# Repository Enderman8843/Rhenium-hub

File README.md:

# Rhenium HUB
It is Hi-Speed USB HUB with USB2514B_B Chip and 24mhz crystal , With Support of USB C aswell as USB A

## How To Use ?
JUST PlUG IT INTO YOUR COMPUTER VIA THE INPUT

## PCB Layout and Render

| PCB | Schematics / Wiring |
|---|---|
| 
 |
|

| 3D View Rear | |
|---|---|

| Case |

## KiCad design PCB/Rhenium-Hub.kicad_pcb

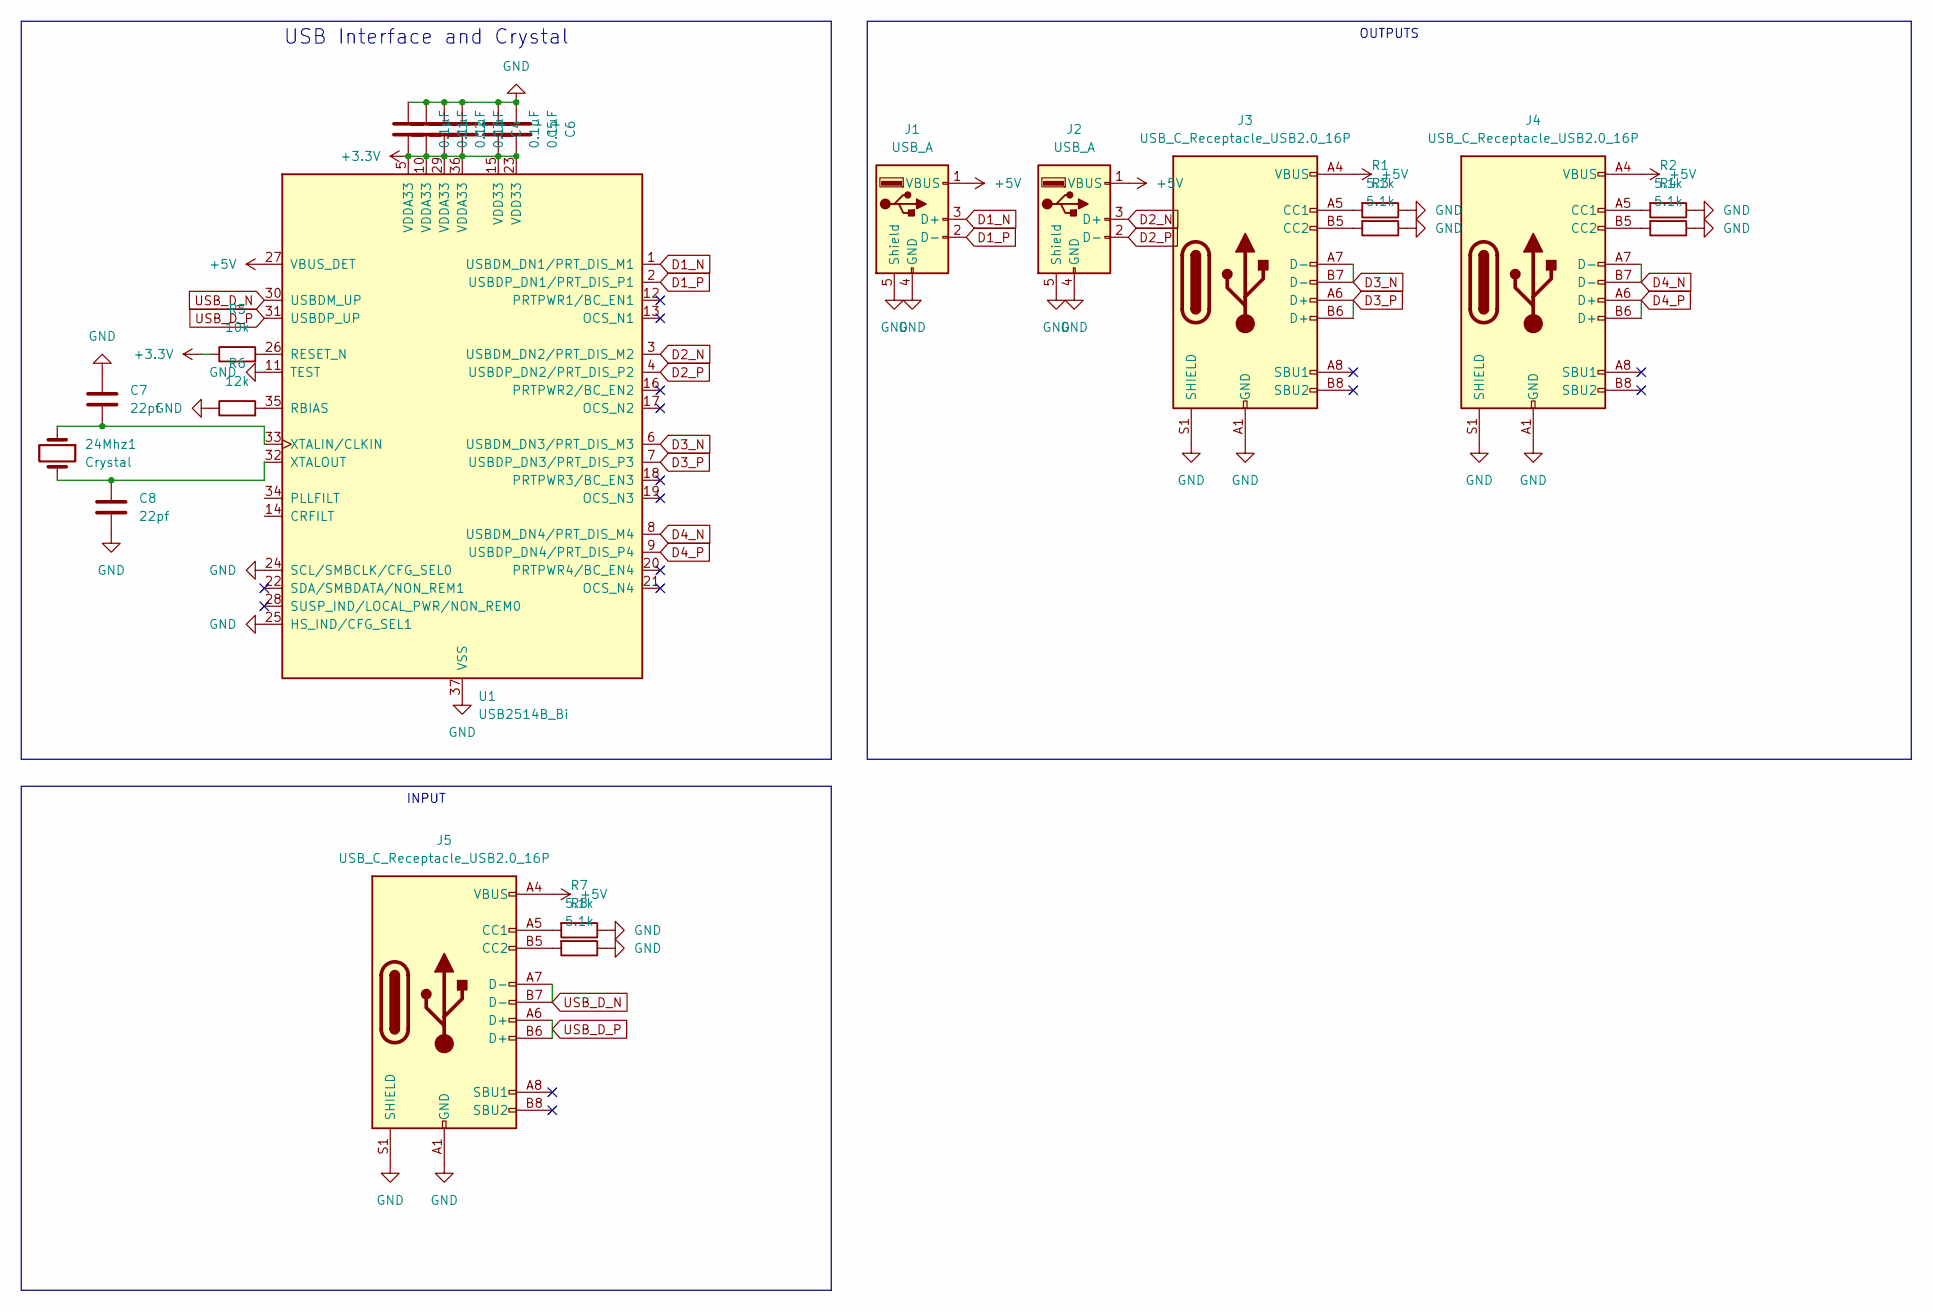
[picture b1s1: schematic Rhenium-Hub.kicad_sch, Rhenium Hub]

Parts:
24Mhz1: Crystal; Crystal_SMD_3225-4Pin_3.2x2.5mm
C1, C2, C3, C4, C5, C6: 0.1µF; C_0603_1608Metric
C7, C8: 22pf; C_0603_1608Metric
J1, J2: USB_A; USB_A_CNCTech_1001-011-01101_Horizontal
J3, J4, J5: USB_C_Receptacle_USB2.0_16P; USB_C_Receptacle_G-Switch_GT-USB-7010ASV
R1, R2, R3, R4, R7, R8: 5.1k; C_0603_1608Metric
R5: 10k; C_0603_1608Metric
R6: 12k; C_0603_1608Metric
U1: USB2514B_Bi; QFN-36-1EP_6x6mm_P0.5mm_EP3.7x3.7mm

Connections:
+3.3V: C1.2, C2.2, C3.2, C4.2, C5.2, C6.2, R5.1, U1.5 (VDDA33), U1.10 (VDDA33), U1.15 (VDD33), U1.23 (VDD33), U1.29 (VDDA33), U1.36 (VDDA33)
+5V: J1.1 (VBUS), J2.1 (VBUS), J3.A4 (VBUS), J3.A9 (VBUS), J3.B4 (VBUS), J3.B9 (VBUS), J4.A4 (VBUS), J4.A9 (VBUS), J4.B4 (VBUS), J4.B9 (VBUS), J5.A4 (VBUS), J5.A9 (VBUS), J5.B4 (VBUS), J5.B9 (VBUS), U1.27 (VBUS_DET)
D1_N: J1.3 (D+), U1.1 (USBDM_DN1/PRT_DIS_M1)
D1_P: J1.2 (D-), U1.2 (USBDP_DN1/PRT_DIS_P1)
D2_N: J2.3 (D+), U1.3 (USBDM_DN2/PRT_DIS_M2)
D2_P: J2.2 (D-), U1.4 (USBDP_DN2/PRT_DIS_P2)
D3_N: J3.A7 (D-), J3.B7 (D-), U1.6 (USBDM_DN3/PRT_DIS_M3)
D3_P: J3.A6 (D+), J3.B6 (D+), U1.7 (USBDP_DN3/PRT_DIS_P3)
D4_N: J4.A7 (D-), J4.B7 (D-), U1.8 (USBDM_DN4/PRT_DIS_M4)
D4_P: J4.A6 (D+), J4.B6 (D+), U1.9 (USBDP_DN4/PRT_DIS_P4)
GND: C1.1, C2.1, C3.1, C4.1, C5.1, C6.1, C7.1, C8.2, J1.4 (GND), J1.5 (Shield), J2.4 (GND), J2.5 (Shield), J3.A1 (GND), J3.A12 (GND), J3.B1 (GND), J3.B12 (GND), J3.S1 (SHIELD), J4.A1 (GND), J4.A12 (GND), J4.B1 (GND), J4.B12 (GND), J4.S1 (SHIELD), J5.A1 (GND), J5.A12 (GND), J5.B1 (GND), J5.B12 (GND), J5.S1 (SHIELD), R1.1, R2.1, R3.1, R4.1, R6.1, R7.1, R8.1, U1.11 (TEST), U1.24 (SCL/SMBCLK/CFG_SEL0), U1.25 (HS_IND/CFG_SEL1), U1.37 (VSS)
unnamed: J3.A5 (CC1), R1.2
unnamed: J3.B5 (CC2), R3.2
unnamed: J4.A5 (CC1), R2.2
unnamed: J4.B5 (CC2), R4.2
unnamed: J5.A5 (CC1), R7.2
unnamed: J5.B5 (CC2), R8.2
unnamed: R6.2, U1.35 (RBIAS)
unnamed: R5.2, U1.26 (RESET_N)
unnamed: 24Mhz1.1, C7.2, U1.33 (XTALIN/CLKIN)
unnamed: 24Mhz1.2, C8.1, U1.32 (XTALOUT)
USB_D_N: J5.A7 (D-), J5.B7 (D-), U1.30 (USBDM_UP)
USB_D_P: J5.A6 (D+), J5.B6 (D+), U1.31 (USBDP_UP)

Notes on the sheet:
INPUT
USB Interface and Crystal
OUTPUTS

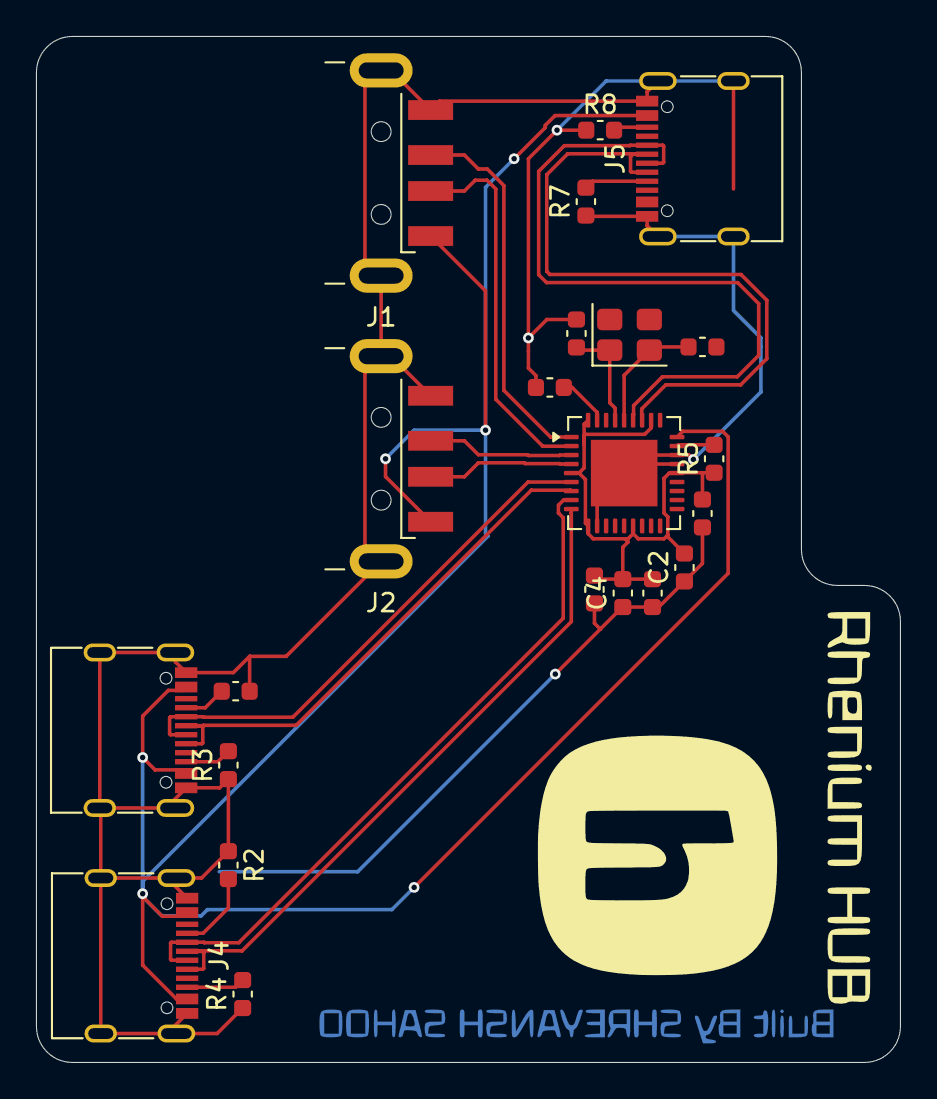
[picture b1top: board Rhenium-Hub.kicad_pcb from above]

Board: 2 copper layers, 48.0 x 57.0 mm, 22 parts (0 on the bottom side), 23 nets.

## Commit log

2026-05-14 Added ALL
